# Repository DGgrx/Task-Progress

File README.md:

# Task Progress

I downloaded Kicad and searched for articles regarding PWM using Arduino. I found these interesting links in the process:

* https://www.youtube.com/c/PlumPot/playlists (KiCad Playlist)
* https://www.arduino.cc/en/pmwiki.php?n=Tutorial/SecretsOfArduinoPWM (Arduino PWM)
* https://forum.arduino.cc/t/pwm-for-a-complete-noob/341473/9
* https://www.arduino.cc/reference/en/language/structure/bitwise-operators/bitwiseand/
* https://krprojects.wordpress.com/2014/05/28/arduino-timers/

I understood how PWM is working. Understood Normal mode, Clear Timer on Compare Match (CTC) Mode and Fast PWM.

In terms of the light follower i added the elements in the schematic and have to proceed further.

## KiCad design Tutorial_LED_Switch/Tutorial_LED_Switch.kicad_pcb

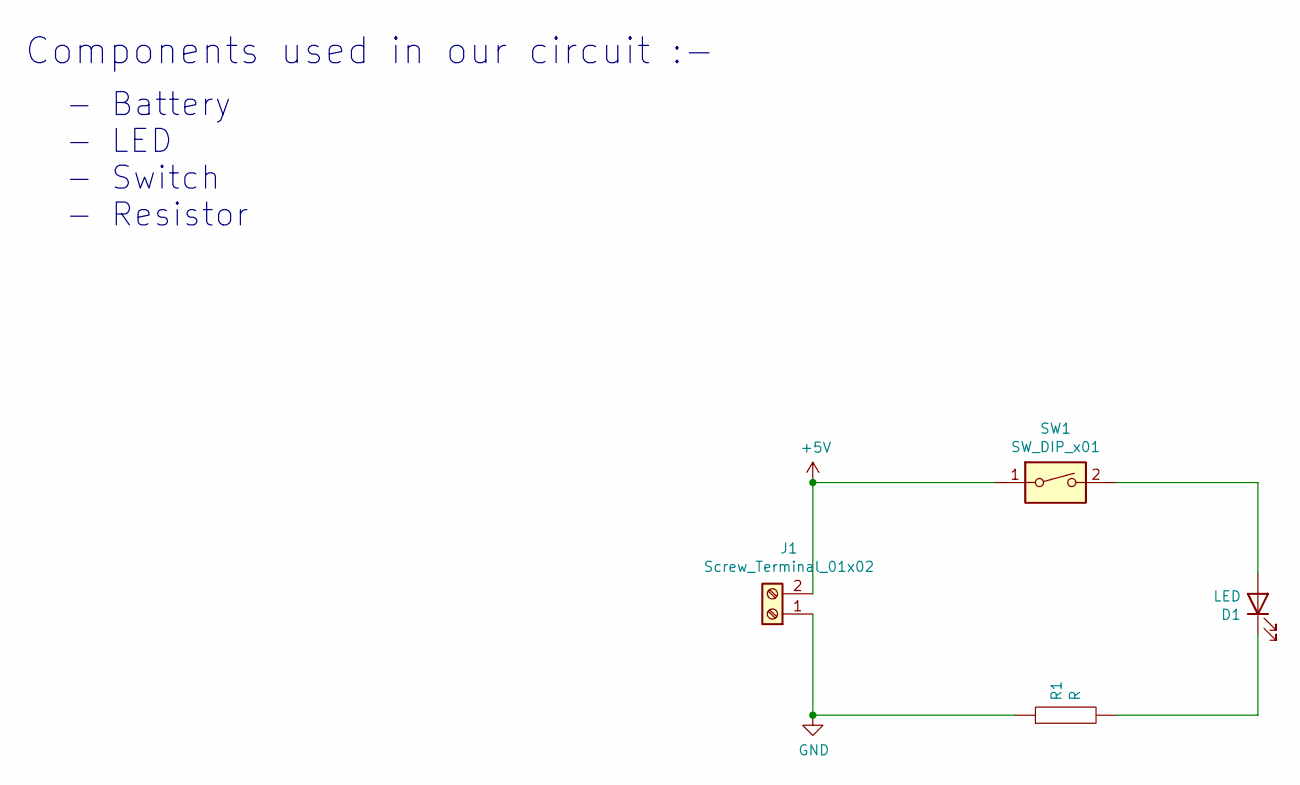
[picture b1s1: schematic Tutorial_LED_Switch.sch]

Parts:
D1: LED
J1: Screw_Terminal_01x02
R1: R
SW1: SW_DIP_x01

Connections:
+5V: J1.2, SW1.1
GND: J1.1, R1.1
unnamed: D1.1 (K), R1.2
unnamed: D1.2 (A), SW1.2

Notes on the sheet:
Components used in our circuit :-
- Battery - LED - Switch - Resistor

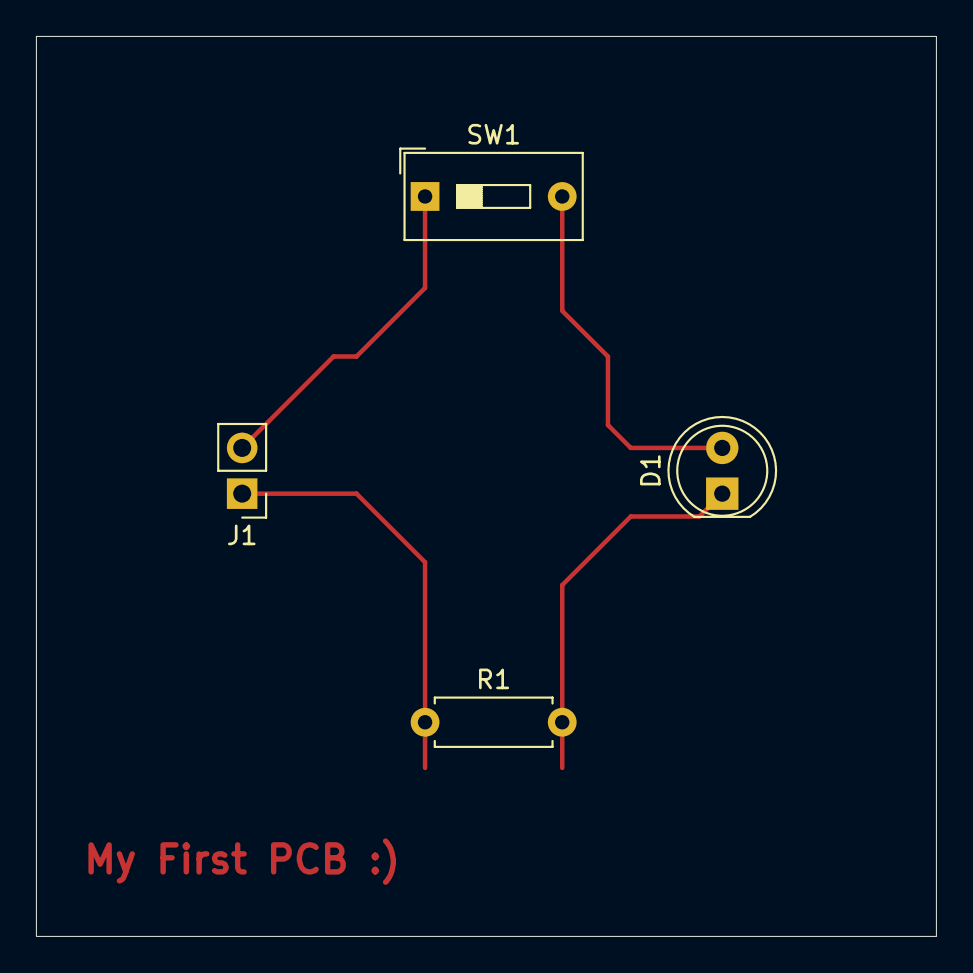
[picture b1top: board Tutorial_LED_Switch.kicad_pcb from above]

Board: 2 copper layers, 50.0 x 50.0 mm, 4 parts (0 on the bottom side), 4 nets.

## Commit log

2021-10-20 Found Sources
2021-10-23 Mady my first PCB :)
2021-10-23 Read the datasheet
2021-10-24 Added elements in the schematic for light follower
2021-10-27 Forgot to push the schematic before :')
    Manually pushed the folder.
2021-10-27 Added PCB Design and LDR Modules
